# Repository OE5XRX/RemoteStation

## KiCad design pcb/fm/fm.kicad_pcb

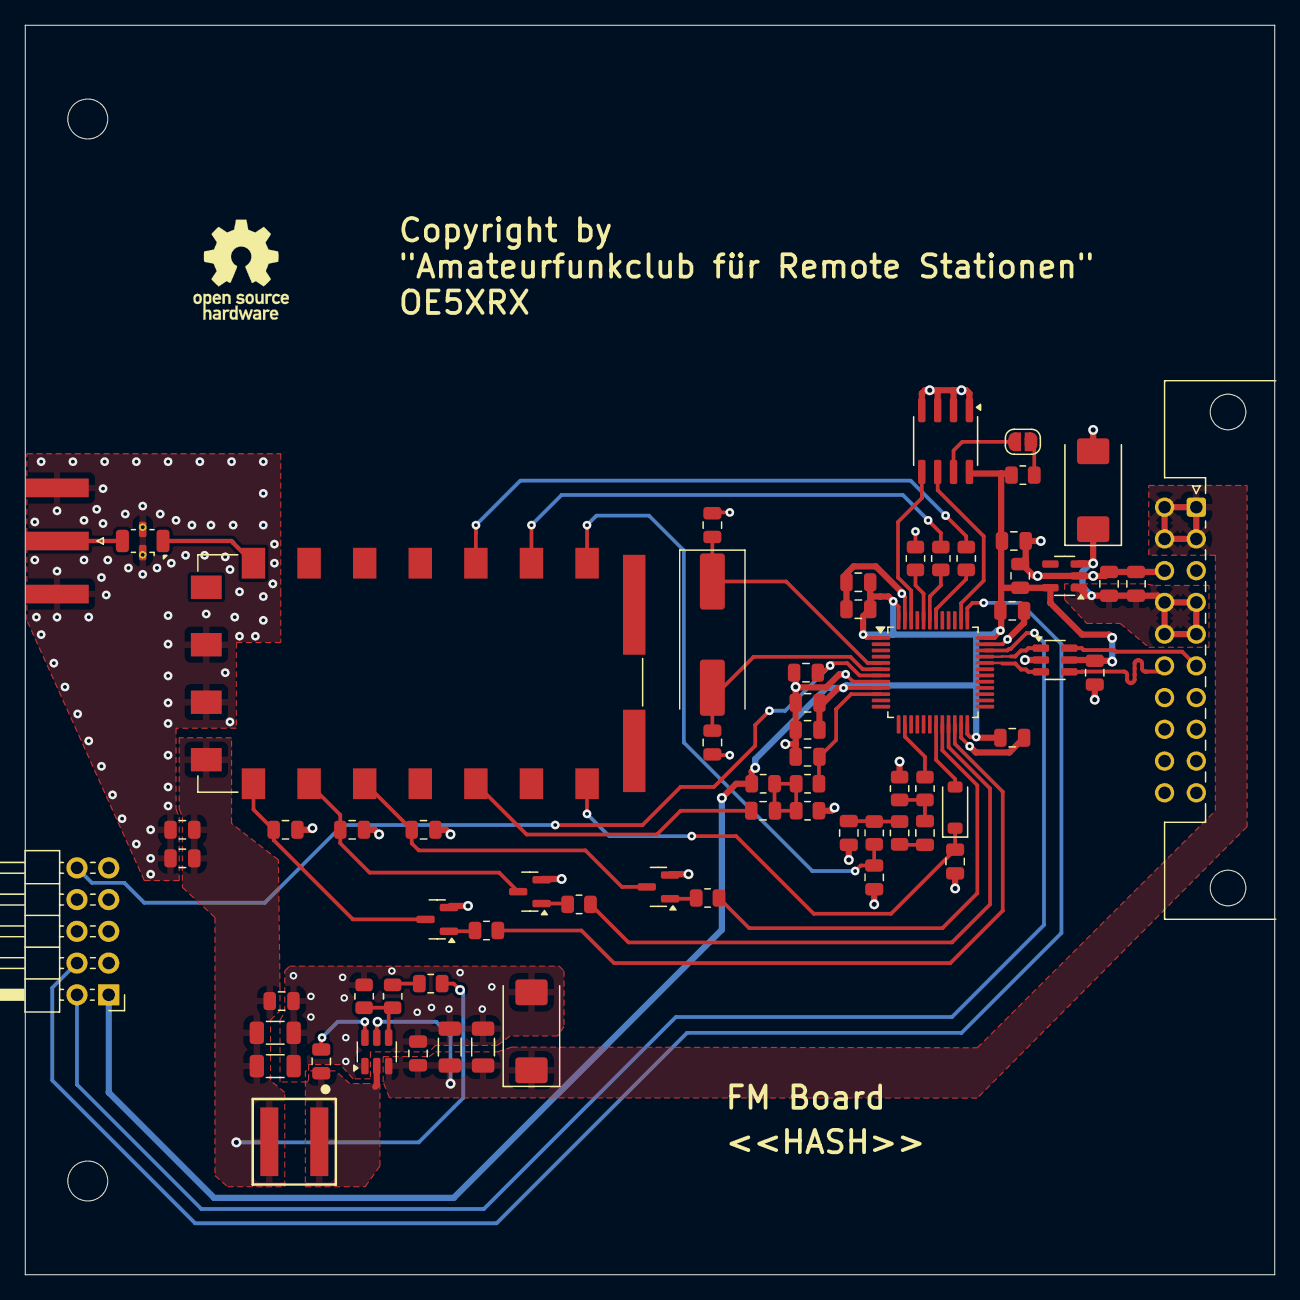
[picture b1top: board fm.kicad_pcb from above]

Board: 4 copper layers, 100.0 x 100.0 mm, 70 parts (0 on the bottom side), 48 nets.

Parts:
C101, C201, C202, C204, C206, C208, C210, C214, C215: 100nF; C_0805_2012Metric
C102: 10uF; C_0805_2012Metric
C103, C402, C501, C601, C701: 10nF/NP0; C_0805_2012Metric
C104, C213: 100u / 25V; CP_EIA-7343-43_Kemet-X
C203, C205: 30pF; C_0805_2012Metric
C207, C209, C301, C401: 4.7u/10V/X5R; C_0805_2012Metric
C211, C212: 1uF; C_0805_2012Metric
C302, C303: 5.6nF/X7R/100V; C_0805_2012Metric
C802, C803: 10u; C_1206_3216Metric
C804, C805, C808: 100n; C_0805_2012Metric
C806, C807: 22u; C_1206_3216Metric
D101: BAT43W-V; D_SOD-123
FL101: LFCN-180/490; Filter_Mini-Circuits_FV1206
H101, H102: MountingHole; MountingHole_3.2mm_M3
J101: Conn_Coaxial; SMA_Amphenol_132289_EdgeMount
J201: Conn_ARM_JTAG_SWD_10; PinHeader_2x05_P2.54mm_Horizontal
J202: Conn_02x10_Row_Letter_First; PCN10C-20S-2.54DS
JP201: SolderJumper_2_Open; SolderJumper-2_P1.3mm_Open_RoundedPad1.0x1.5mm
L801: 6.8u; WE-XHMI_6060
Q501, Q601, Q701: 2N7002; SOT-23
R101, R102: 220; R_0805_2012Metric
R201, R403: 2k2; R_0805_2012Metric
R202: 3k9; R_0805_2012Metric
R301: 56k; R_0805_2012Metric
R302, R303, R304, R501, R601, R701: 10k; R_0805_2012Metric
R401, R402: 5k1; R_0805_2012Metric
R801: 49R9; R_0805_2012Metric
R802: 100k; R_0805_2012Metric
R803: 13k7; R_0805_2012Metric
U101: SA818V; DRA818
U201: STM32F302CBTx; LQFP-48_7x7mm_P0.5mm
U202: CAT24C32; SOIC-8_3.9x4.9mm_P1.27mm
U203: TLV73333PQDBVRQ1; SOT-23-5
U204: USBLC6-2SC6; SOT-23-6
U801: LMR51430 500kHz; SOT-23-6
Y201: 8MHz / 20pF; Crystal_SMD_HC49-SD

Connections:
+3V3: C202.2, C204.2, C206.2, C207.2, C208.2, C209.2, C212.1, C214.2, C215.1, J201.1 (VTref), R202.1, R401.2, U201.1 (VBAT), U201.9 (VDDA), U201.24 (VDD), U201.36 (VDD), U201.48 (VDD), U202.8 (VCC), U203.5 (OUT), U204.5 (VBUS)
+5V: C210.2, C211.1, C213.1, J202.a4, J202.a5, J202.b4, J202.b5, U203.1 (IN), U203.3 (EN)
+5V_HF: C101.2, C102.2, C806.2, C807.2, C808.2, L801.2, R801.1, U101.8 (VDD)
+12V: C104.1, C802.1, C803.1, C804.1, J202.a1, J202.a2, J202.b1, J202.b2, U801.3 (VIN), U801.5 (EN)
/5V/TPS_SW: C805.2, L801.1, U801.2 (SW)
/ADC: C402.2, R403.2, U201.10 (PA0)
/AF_OUT: C401.2, U101.3 (AF_OUT)
/ANT: FL101.3 (OUT), J101.1 (In)
/Connector and CPU/GPIO4: D101.2 (A), U201.19 (PB1)
/Connector and CPU/I2C_SCL_MEM: U201.38 (PA15), U202.6 (SCL)
/Connector and CPU/I2C_SDA_MEM: U201.46 (PB9), U202.5 (SDA)
/Connector and CPU/NS_USB+: U201.33 (PA12), U204.1 (I/O1)
/Connector and CPU/NS_USB-: U201.32 (PA11), U204.3 (I/O2)
/Connector and CPU/SWCLK: J201.4 (SWCLK/TCK), U201.37 (PA14)
/Connector and CPU/SWDIO: J201.2 (SWDIO/TMS), U201.34 (PA13)
/Connector and CPU/USART_RX: R102.2, U201.43 (PB7)
/Connector and CPU/USART_TX: R101.2, U201.42 (PB6)
/Connector and CPU/USB+: J202.a6, U204.6 (I/O1)
/Connector and CPU/USB-: J202.b6, U204.4 (I/O2)
/Connector and CPU/nRESET: C201.1, J201.10 (~RESET), U201.7 (NRST)
/DAC: R301.1, U201.14 (PA4)
/GPIO1: R601.1, U201.20 (PB2)
/GPIO2: R701.1, U201.21 (PB10)
/GPIO3: R501.1, U201.22 (PB11)
/H_L_Power: C501.2, Q501.3 (D), U101.7 (H/L)
/LPF: FL101.1 (IN), U101.12 (ANT)
/MIC_IN: C303.1, R304.2, U101.18 (MIC_IN)
/RADIO_RX: R101.1, U101.16 (RXD)
/RADIO_TX: R102.1, U101.17 (TXD)
/nPOWER_DOWN: C701.2, Q701.3 (D), U101.6 (~PD)
/nPTT: C601.2, Q601.3 (D), U101.5 (~PTT)
/nSQUELCH: C103.2, D101.1 (K), U101.1 (~SQ)
GND: C101.1, C102.1, C103.1, C104.2, C201.2, C202.1, C203.2, C204.1, C205.2, C206.1, C207.1, C208.1, C209.1, C210.1, C211.2, C212.2, C213.2, C214.1, C215.2, C302.2, C303.2, C402.1, C501.1, C601.1, C701.1, C802.2, C803.2, C804.2, C806.1, C807.1, C808.1, FL101.2 (GND), FL101.4 (GND), J101.2 (Ext), J201.3 (GND), J201.5 (GND), J201.9 (GNDDetect), J202.a3, J202.a10, J202.b3, J202.b10, Q501.2 (S), Q601.2 (S), Q701.2 (S), R201.2, R302.2, R402.1, R803.2, U101.9 (GND), U101.10 (GND), U201.8 (VSSA), U201.23 (VSS), U201.35 (VSS), U201.47 (VSS), U202.1 (A0), U202.2 (A1), U202.3 (A2), U202.4 (GND), U203.2 (GND), U204.2 (GND), U801.1 (GND)
unnamed: C301.1, R303.1
unnamed: C301.2, R301.2, R302.1
unnamed: C302.1, R303.2, R304.1
unnamed: C401.1, R401.1, R402.2, R403.1
unnamed: JP201.1 (A), U202.7 (WP)
unnamed: JP201.2 (B), R202.2
unnamed: Q501.1 (G), R501.2
unnamed: Q601.1 (G), R601.2
unnamed: Q701.1 (G), R701.2
unnamed: R801.2, R802.1
unnamed: R201.1, U201.44 (BOOT0)
unnamed: C203.1, U201.5 (PF0), Y201.1
unnamed: C205.1, U201.6 (PF1), Y201.2
unnamed: C805.1, U801.6 (CB)
unnamed: R802.2, R803.1, U801.4 (FB)

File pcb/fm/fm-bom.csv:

Row,Description,Part,References,Value,Footprint,Quantity Per PCB,Status,Datasheet,LCSC,MOUSER,SnapEDA_Link
1,Unpolarized capacitor,C,C203 C205,30pF,C_0805_2012Metric,2, ,~,,791-0805N300J500CT,
2,Unpolarized capacitor,C,C302 C303,5.9nF,C_0805_2012Metric,2, ,~,,,
3,Unpolarized capacitor,C,C103 C402 C501 C601 C701,10nF/NP0,C_0805_2012Metric,5, ,~,,81-GRM2165C2A103JA1D,
4,Unpolarized capacitor,C,C101 C106 C201 C202 C204 C206 C208 C210 C214,100nF,C_0805_2012Metric,9, ,~,C28233,,
5,Unpolarized capacitor,C,C104 C211 C212,1uF,C_0805_2012Metric,3, ,~,,791-0805B105K250CT,
6,Unpolarized capacitor,C,C105,2.2uF,C_0805_2012Metric,1, ,~,,187-CL21B225KOFNNNG,
7,Unpolarized capacitor,C,C102,10uF,C_0805_2012Metric,1, ,~,,963-EMK212BJ106KG-T,
8,Polarized capacitor,C_Polarized,C213,100u / 25V,CP_EIA-7343-43_Kemet-X,1, ,~,C132558,,
9,Unpolarized capacitor,C,C207 C209 C301 C401,4.7u/10V/X5R,C_0805_2012Metric,4, ,~,,187-CL21A475KAQNNNF,
10,"30V 0.2A Small Signal Schottky diode, SOD-123",BAT43W-V,D101,BAT43W-V,D_SOD-123,1, ,http://www.vishay.com/docs/85660/bat42.pdf,,78-BAT43W-G3-08,
11,"180MHz/490MHz 50 Ohm Passive Low Pass Filter, FV1206",LFCN-160,FL101,LFCN-180/490,Filter_Mini-Circuits_FV1206,1, ,https://www.minicircuits.com/pdfs/LFCN-180+.pdf,,139-LFCN-180 / 139-LFCN-490,
12,"Generic connector, double row, 02x10, row letter first pin numbering scheme (pin number consists of a letter for the row and a number for the pin index in this row. a1, ..., aN; b1, ..., bN), script generated (kicad-library-utils/schlib/autogen/connector/)",Conn_02x10_Row_Letter_First,J202,Conn_02x10_Row_Letter_First,PCN10C-20S-2.54DS,1, ,~,,798-PCN10C20S254DS72,
13,"Cortex Debug Connector, standard ARM Cortex-M SWD and JTAG interface",Conn_ARM_JTAG_SWD_10,J201,Conn_ARM_JTAG_SWD_10,PinHeader_2x05_P2.54mm_Horizontal,1, ,http://infocenter.arm.com/help/topic/com.arm.doc.ddi0314h/DD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,,,
14,"coaxial connector (BNC, SMA, SMB, SMC, Cinch/RCA, LEMO, ...)",Conn_Coaxial,J101,Conn_Coaxial,SMA_Amphenol_132289_EdgeMount,1, ,~,,530-142-0701-801,
15,"0.115A Id, 60V Vds, N-Channel MOSFET, SOT-23",2N7002,Q501 Q601 Q701,2N7002,SOT-23,3, ,https://www.onsemi.com/pub/Collateral/NDS7002A-D.PDF,,637-2N7002,
16,Resistor,R,R101 R102,220,R_0805_2012Metric,2, ,~,,667-ERA-6AEB221V,
17,Resistor,R,R201 R403,2k2,R_0805_2012Metric,2, ,~,C17520,,
18,Resistor,R,R202,3k9,R_0805_2012Metric,1, ,~,,603-RT0805DRD073K9L,
19,Resistor,R,R401 R402,5k1,R_0805_2012Metric,2, ,~,C27834,,
20,Resistor,R,R302 R303 R304 R501 R601 R701,10k,R_0805_2012Metric,6, ,~,,603-RT0805DRE0710KL,
21,Resistor,R,R301,56k,R_0805_2012Metric,1, ,~,,,
22,"32 kb CMOS Serial EEPROM, SOIC-8/TSSOP-8/DFN-8",CAT24C128,U202,CAT24C32,SOIC-8_3.9x4.9mm_P1.27mm,1, ,,,698-CAT24C32WI-GT3,
23,,SA818V,U101,SA818V,DRA818,1, ,,C3001504,,https://www.snapeda.com/parts/DRA818V/DORJI/view-part/?ref=snap
24,"STMicroelectronics Arm Cortex-M4 MCU, 128KB flash, 32KB RAM, 72 MHz, 2.0-3.6V, 37 GPIO, LQFP48",STM32F302CBTx,U201,STM32F302CBTx,LQFP-48_7x7mm_P0.5mm,1, ,https://www.st.com/resource/en/datasheet/stm32f302cb.pdf,,511-STM32F302CBT7,
25,"300mA Capacitor-Free Low Dropout Voltage Regulator, Fixed Output 3.3V, SOT-23-5",TLV73333PDBV,U203,TLV73333PQDBVRQ1,SOT-23-5,1, ,http://www.ti.com/lit/ds/symlink/tlv733p.pdf,C2862550,595-TLV73333PQDBVRQ1,
26,,XC6220B331MR,U102,XC6227C401PR-G,SOT-89-5,1, ,,,865-XC6227C401PR-G,
27,Two pin crystal,Crystal,Y201,8MHz / 20pF,Crystal_SMD_HC49-SD,1, ,~,,73-XT49M800-20,

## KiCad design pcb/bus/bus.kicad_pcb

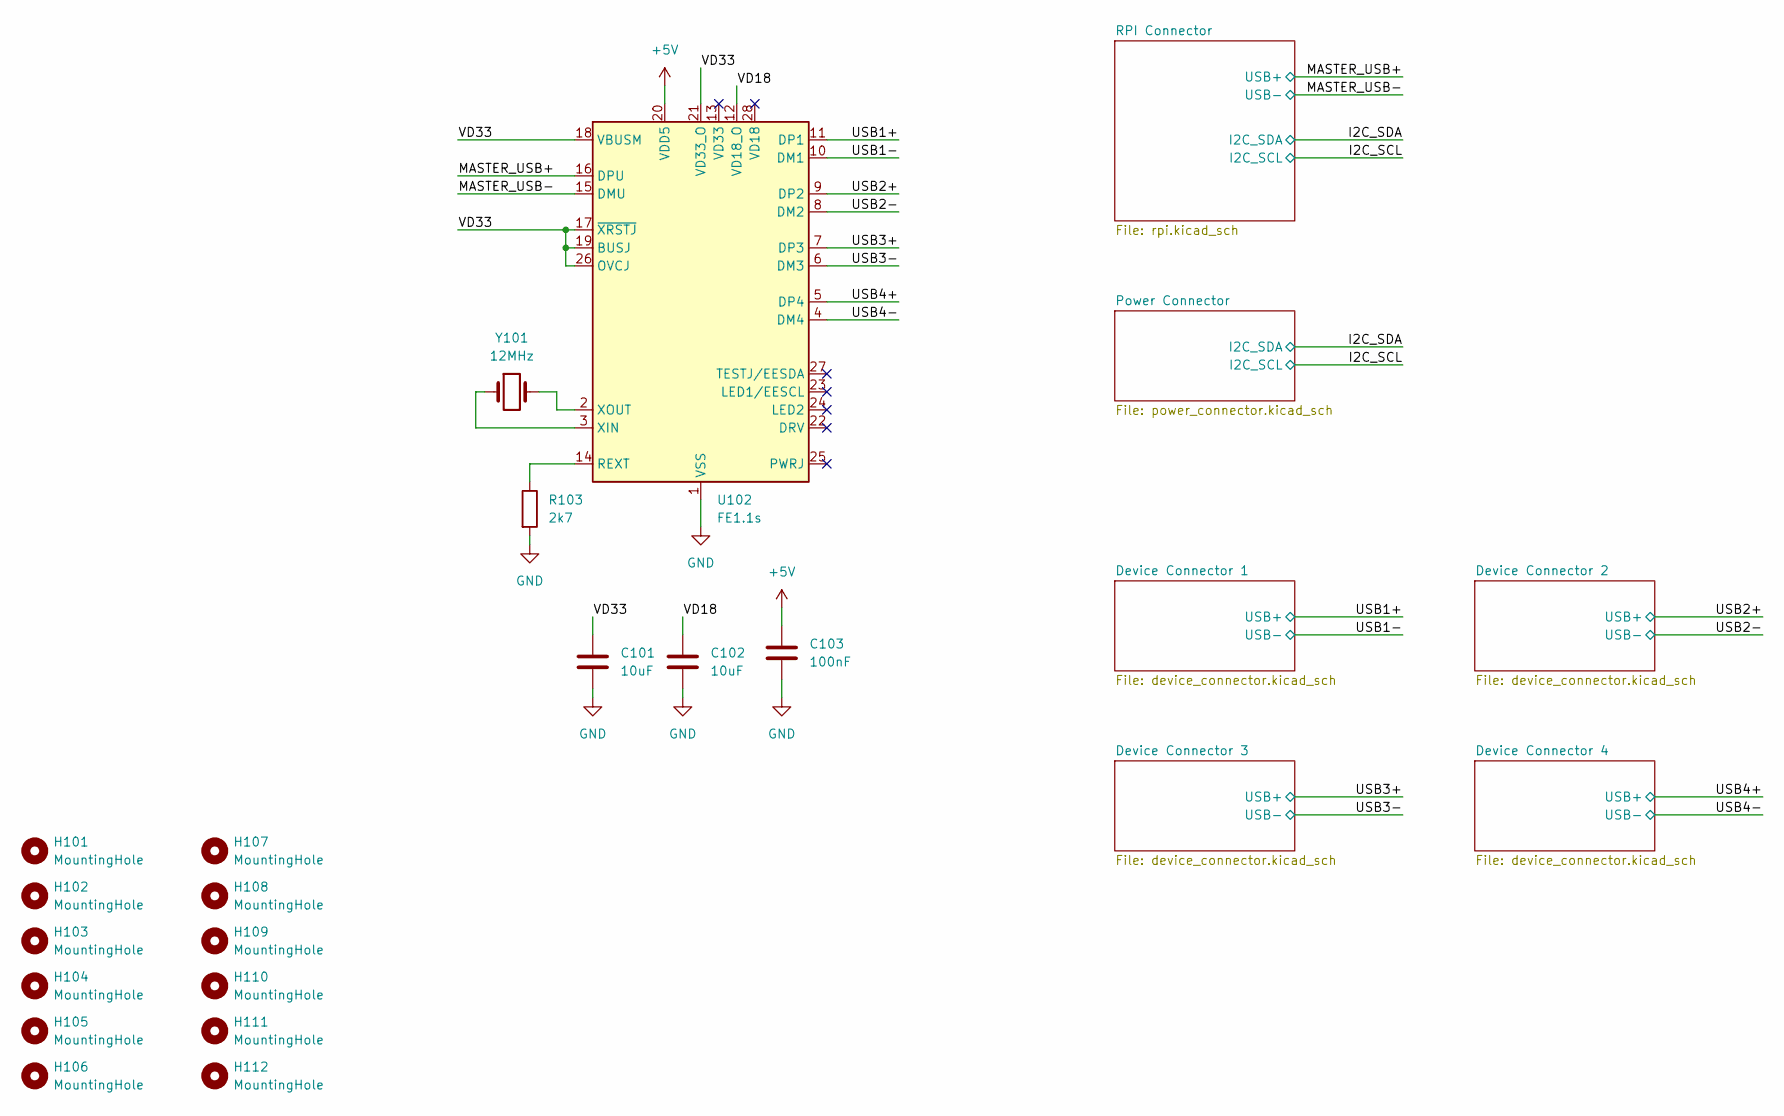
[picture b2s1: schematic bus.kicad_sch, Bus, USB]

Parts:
C101, C102: 10uF; C_0805_2012Metric; LCSC C13585
C103: 100nF; C_0805_2012Metric; LCSC C28233
H101, H102, H103, H104, H105, H106, H107, H108, H109, H110, H111, H112: MountingHole; MountingHole_3.2mm_M3
R103: 2k7; R_0805_2012Metric; LCSC C352230
U102: FE1.1s; SSOP-28_3.9x9.9mm_P0.635mm; LCSC C6706491
Y101: 12MHz; M49S-SMD; LCSC C2983432

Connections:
+5V: C103.1, U102.20 (VDD5); also elsewhere on the board
/MASTER_USB+: U102.16 (DPU); also elsewhere on the board
/MASTER_USB-: U102.15 (DMU); also elsewhere on the board
/USB1+: U102.5 (DP4); also elsewhere on the board
/USB1-: U102.4 (DM4); also elsewhere on the board
/USB2+: U102.7 (DP3); also elsewhere on the board
/USB2-: U102.6 (DM3); also elsewhere on the board
/USB3+: U102.9 (DP2); also elsewhere on the board
/USB3-: U102.8 (DM2); also elsewhere on the board
/USB4+: U102.11 (DP1); also elsewhere on the board
/USB4-: U102.10 (DM1); also elsewhere on the board
/VD18: C102.1, U102.12 (VD18_O)
/VD33: C101.1, U102.17 (~XRSTJ), U102.18 (VBUSM), U102.19 (BUSJ), U102.21 (VD33_O), U102.26 (OVCJ)
GND: C101.2, C102.2, C103.2, R103.2, U102.1 (VSS); also elsewhere on the board
unnamed: R103.1, U102.14 (REXT)
unnamed: U102.3 (XIN), Y101.1
unnamed: U102.2 (XOUT), Y101.2

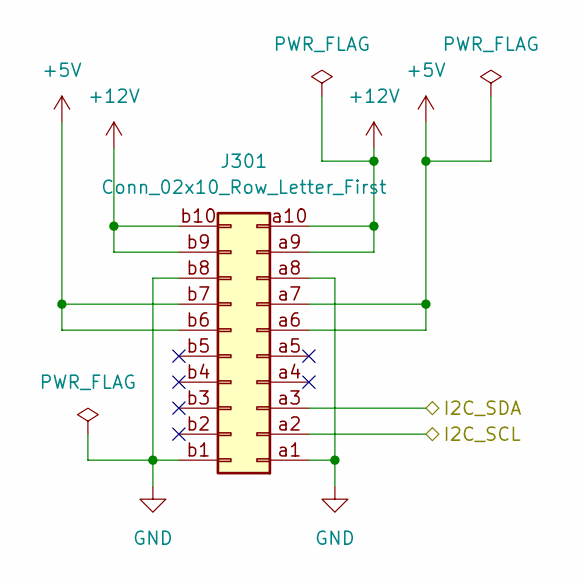
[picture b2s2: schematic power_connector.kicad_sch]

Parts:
J301: Conn_02x10_Row_Letter_First; PCN10-20P-2.54DSA

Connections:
+5V: J301.a6, J301.a7, J301.b6, J301.b7; also elsewhere on the board
+12V: J301.a9, J301.a10, J301.b9, J301.b10; also elsewhere on the board
/I2C_SCL: J301.a2; also elsewhere on the board
/I2C_SDA: J301.a3; also elsewhere on the board
GND: J301.a1, J301.a8, J301.b1, J301.b8; also elsewhere on the board

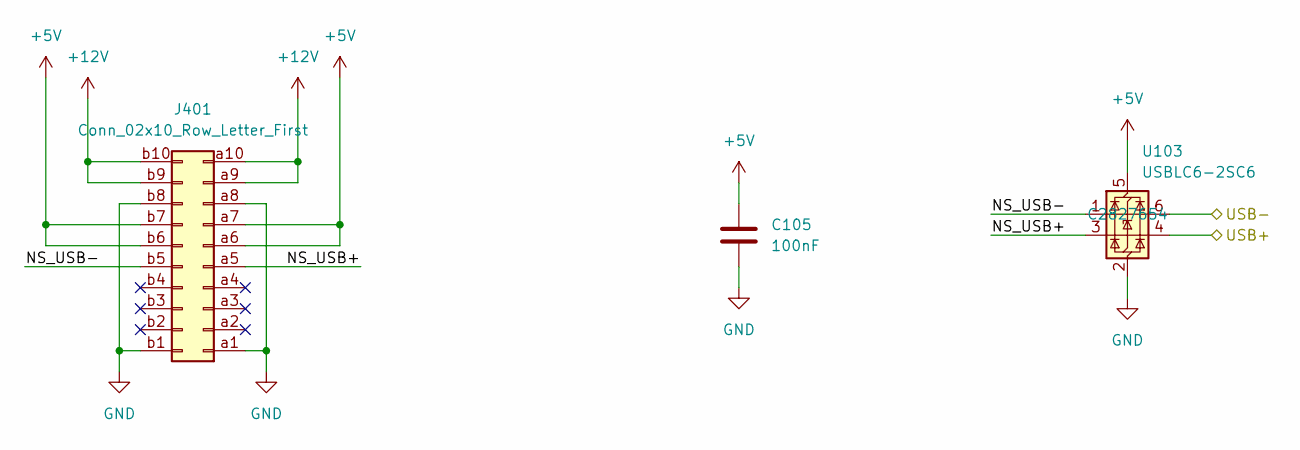
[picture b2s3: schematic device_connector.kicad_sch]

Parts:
C105: 100nF; C_0805_2012Metric; LCSC C28233
J401: Conn_02x10_Row_Letter_First; PCN10-20P-2.54DSA; MOUSER 798-PCN1020P254DSA72
U103: USBLC6-2SC6; SOT-666; LCSC C2827654

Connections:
+5V: C105.1, J401.a6, J401.a7, J401.b6, J401.b7, U103.5 (VBUS); also elsewhere on the board
+12V: J401.a9, J401.a10, J401.b9, J401.b10; also elsewhere on the board
/Device Connector 1/NS_USB+: J401.a5, U103.3 (I/O2)
/Device Connector 1/NS_USB-: J401.b5, U103.1 (I/O1)
/USB1+: U103.4 (I/O2); also elsewhere on the board
/USB1-: U103.6 (I/O1); also elsewhere on the board
GND: C105.2, J401.a1, J401.a8, J401.b1, J401.b8, U103.2 (GND); also elsewhere on the board

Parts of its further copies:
C106, C107, C108: 100nF; C_0805_2012Metric; LCSC C28233
J501, J601, J701: Conn_02x10_Row_Letter_First; PCN10-20P-2.54DSA; MOUSER 798-PCN1020P254DSA72
U104, U105, U106: USBLC6-2SC6; SOT-666; LCSC C2827654

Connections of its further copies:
+5V: C106.1, C107.1, C108.1, J501.a6, J501.a7, J501.b6, J501.b7, J601.a6, J601.a7, J601.b6, J601.b7, J701.a6, J701.a7, J701.b6, J701.b7, U104.5 (VBUS), U105.5 (VBUS), U106.5 (VBUS); also elsewhere on the board
+12V: J501.a9, J501.a10, J501.b9, J501.b10, J601.a9, J601.a10, J601.b9, J601.b10, J701.a9, J701.a10, J701.b9, J701.b10; also elsewhere on the board
/Device Connector 2/NS_USB+: J501.a5, U104.3 (I/O2)
/Device Connector 2/NS_USB-: J501.b5, U104.1 (I/O1)
/Device Connector 3/NS_USB+: J601.a5, U105.3 (I/O2)
/Device Connector 3/NS_USB-: J601.b5, U105.1 (I/O1)
/Device Connector 4/NS_USB+: J701.a5, U106.3 (I/O2)
/Device Connector 4/NS_USB-: J701.b5, U106.1 (I/O1)
/USB2+: U104.4 (I/O2); also elsewhere on the board
/USB2-: U104.6 (I/O1); also elsewhere on the board
/USB3+: U105.4 (I/O2); also elsewhere on the board
/USB3-: U105.6 (I/O1); also elsewhere on the board
/USB4+: U106.4 (I/O2); also elsewhere on the board
/USB4-: U106.6 (I/O1); also elsewhere on the board
GND: C106.2, C107.2, C108.2, J501.a1, J501.a8, J501.b1, J501.b8, J601.a1, J601.a8, J601.b1, J601.b8, J701.a1, J701.a8, J701.b1, J701.b8, U104.2 (GND), U105.2 (GND), U106.2 (GND); also elsewhere on the board

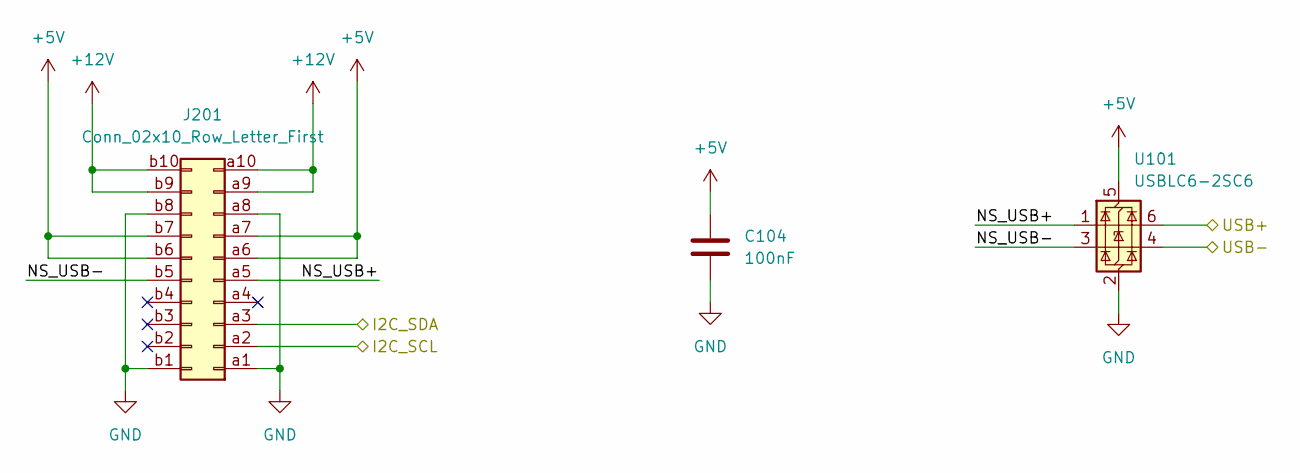
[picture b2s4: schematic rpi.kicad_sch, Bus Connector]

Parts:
C104: 100nF; C_0805_2012Metric; LCSC C28233
J201: Conn_02x10_Row_Letter_First; PCN10-20P-2.54DSA; MOUSER 798-PCN1020P254DSA72
U101: USBLC6-2SC6; SOT-666; LCSC C2827654

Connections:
+5V: C104.1, J201.a6, J201.a7, J201.b6, J201.b7, U101.5 (VBUS); also elsewhere on the board
+12V: J201.a9, J201.a10, J201.b9, J201.b10; also elsewhere on the board
/I2C_SCL: J201.a2; also elsewhere on the board
/I2C_SDA: J201.a3; also elsewhere on the board
/MASTER_USB+: U101.6 (I/O1); also elsewhere on the board
/MASTER_USB-: U101.4 (I/O2); also elsewhere on the board
/RPI Connector/NS_USB+: J201.a5, U101.1 (I/O1)
/RPI Connector/NS_USB-: J201.b5, U101.3 (I/O2)
GND: C104.2, J201.a1, J201.a8, J201.b1, J201.b8, U101.2 (GND); also elsewhere on the board

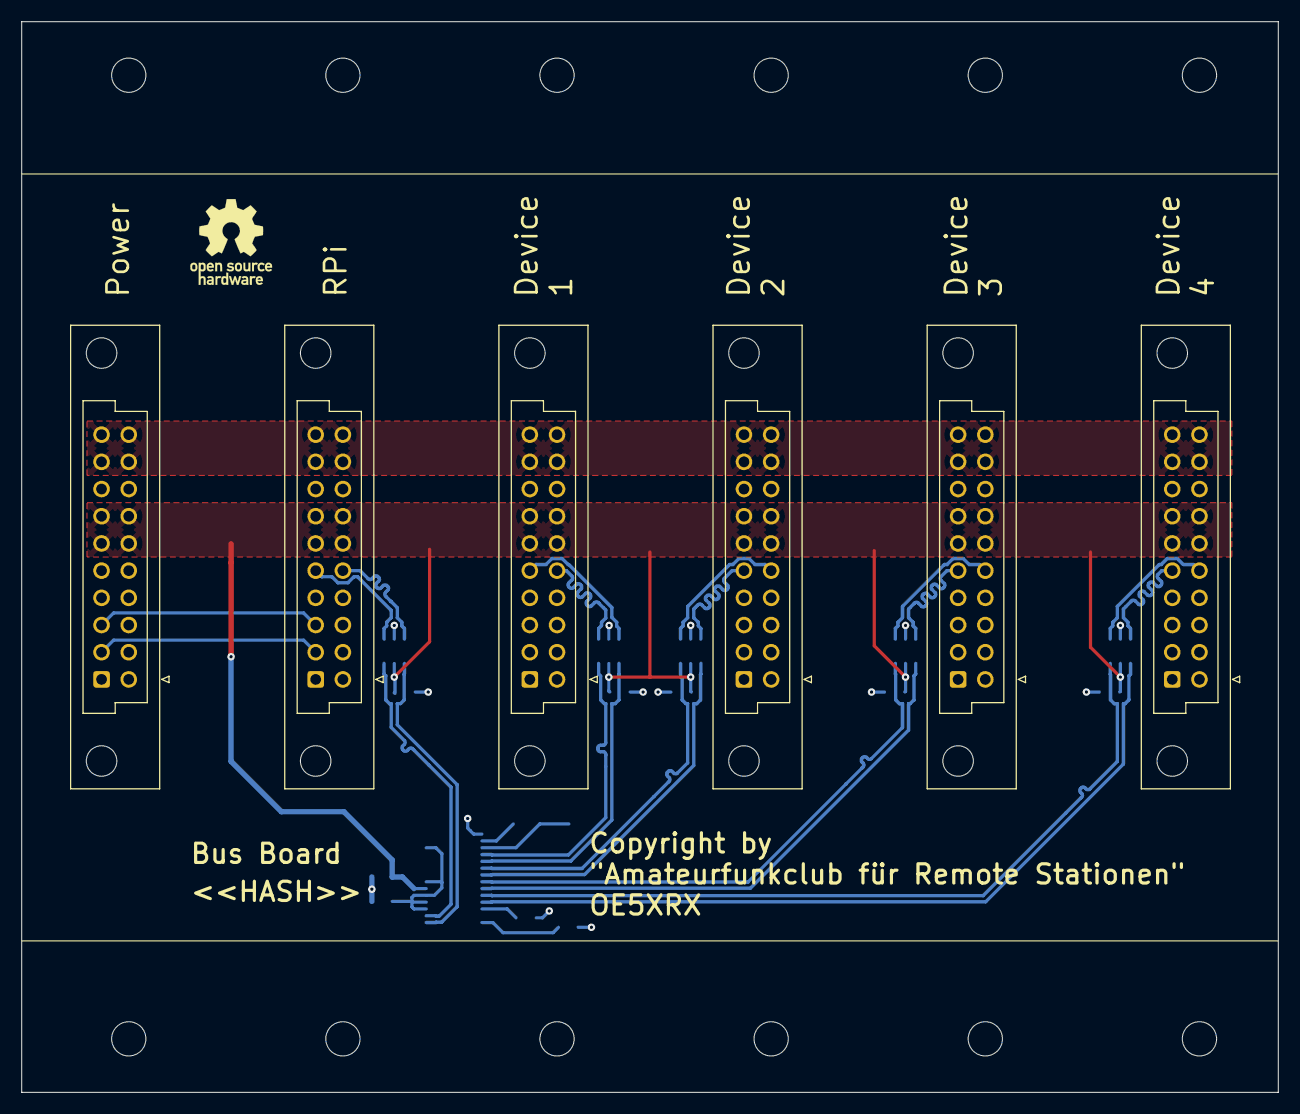
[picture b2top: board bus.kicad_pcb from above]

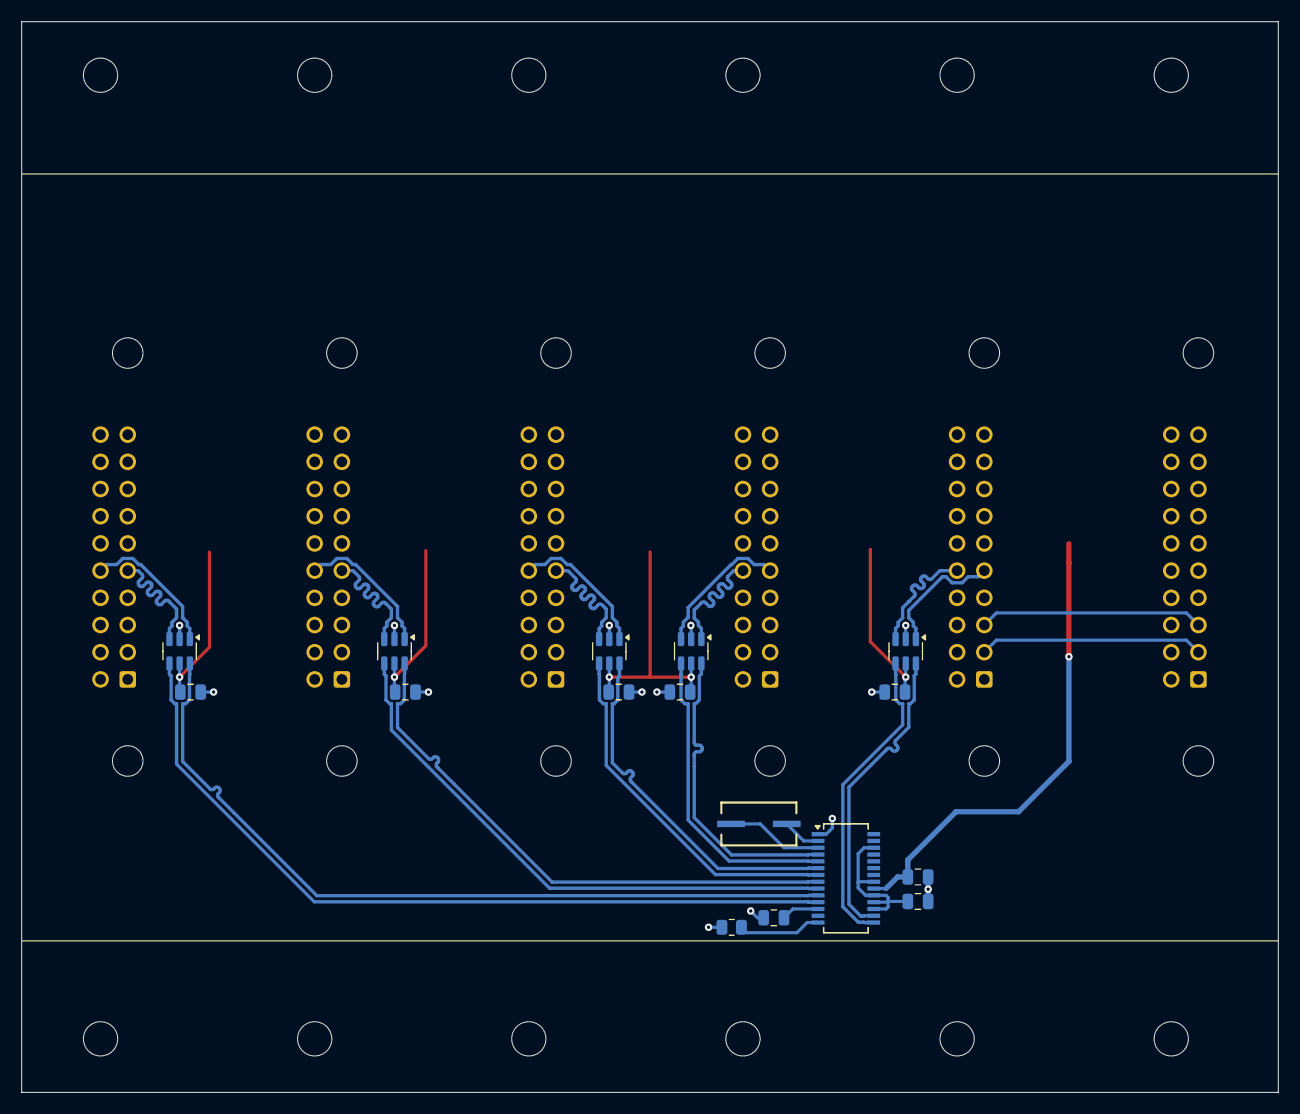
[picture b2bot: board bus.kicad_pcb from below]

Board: 4 copper layers, 117.4 x 100.0 mm, 34 parts (16 on the bottom side), 30 nets.

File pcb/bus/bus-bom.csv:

Row,Description,Part,References,Value,Footprint,Quantity Per PCB,Status,Datasheet,LCSC,MOUSER
1,Unpolarized capacitor,C,C103 C104 C105 C106 C107 C108,100nF,C_0805_2012Metric,6, ,~,C28233,
2,Unpolarized capacitor,C,C101 C102,10uF,C_0805_2012Metric,2, ,~,C13585,
3,"Generic connector, double row, 02x10, row letter first pin numbering scheme (pin number consists of a letter for the row and a number for the pin index in this row. a1, ..., aN; b1, ..., bN), script generated (kicad-library-utils/schlib/autogen/connector/)",Conn_02x10_Row_Letter_First,J201 J301 J401 J501 J601 J701,Conn_02x10_Row_Letter_First,PCN10-20P-2.54DSA,6, ,~,,798-PCN1020P254DSA72
4,Resistor,R,R103,2k7,R_0805_2012Metric,1, ,~,C352230,
5,"USB 2.0 High Speed 4-Port Hub Controller, SSOP-28",FE1.1s,U102,FE1.1s,SSOP-28_3.9x9.9mm_P0.635mm,1, ,https://cdn-shop.adafruit.com/product-files/2991/FE1.1s+Data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,C6706491,
6,"Very low capacitance ESD protection diode, 2 data-line, SOT-23-6",USBLC6-2SC6,U101 U103 U104 U105 U106,USBLC6-2SC6,SOT-666,5, ,https://www.st.com/resource/en/datasheet/usblc6-2.pdf,C2827654,
7,Two pin crystal,Crystal,Y101,12MHz,M49S-SMD,1, ,~,C2983432,

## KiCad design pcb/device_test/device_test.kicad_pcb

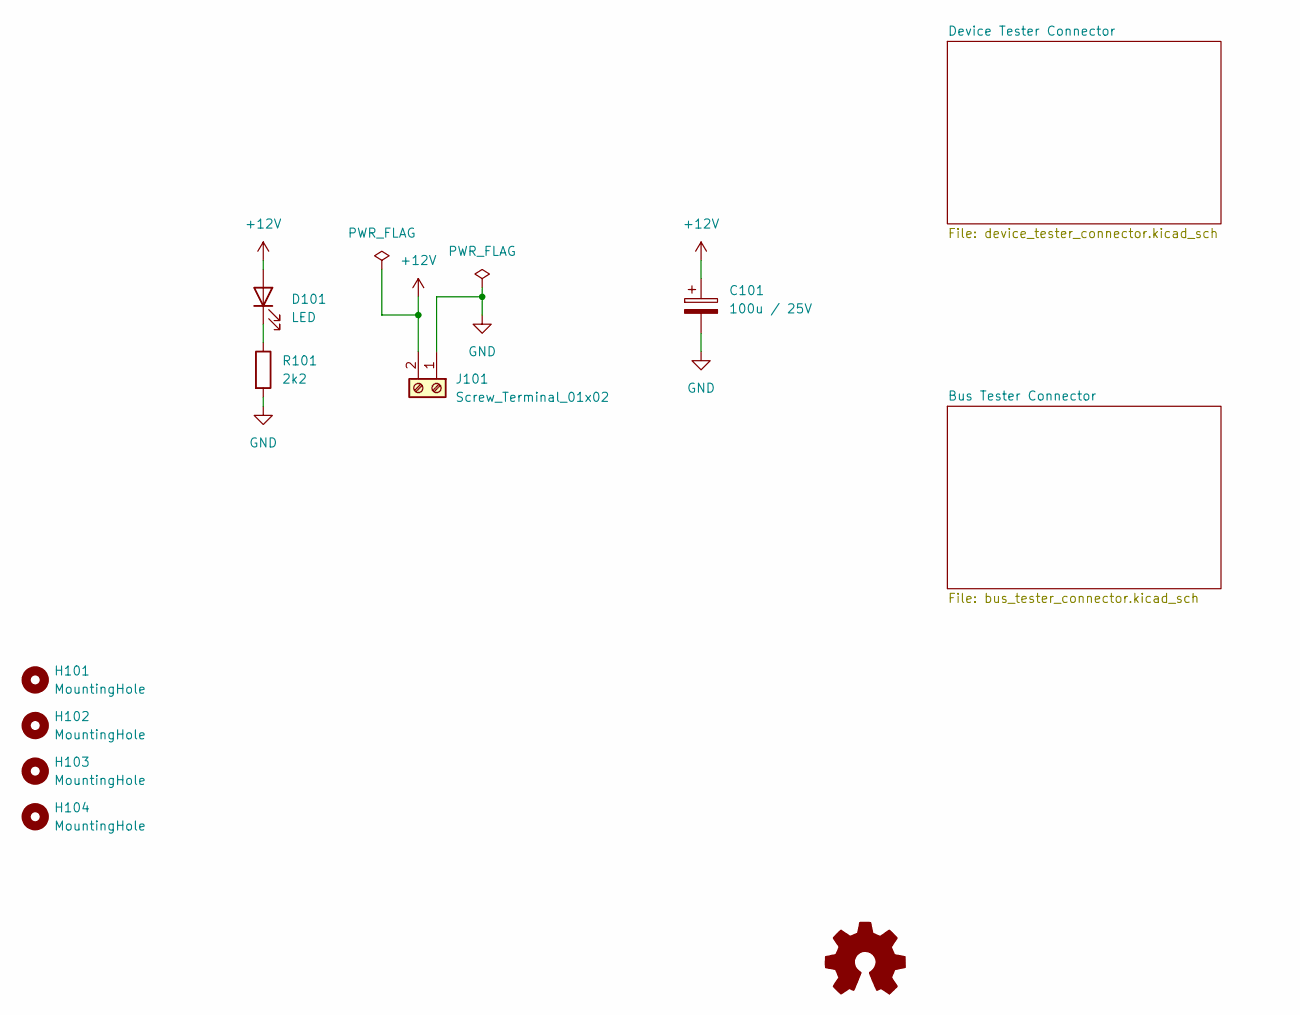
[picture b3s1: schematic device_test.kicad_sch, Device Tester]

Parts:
C101: 100u / 25V; CP_EIA-7343-43_Kemet-X; LCSC C132558
D101: LED; LED_0805_2012Metric; LCSC C84256
H101, H102, H103, H104: MountingHole; MountingHole_3.2mm_M3
J101: Screw_Terminal_01x02; TerminalBlock_Phoenix_MKDS-1,5-2-5.08_1x02_P5.08mm_Horizont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; LCSC C5349557
R101: 2k2; R_0805_2012Metric; LCSC C17520

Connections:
+12V: C101.1, D101.2 (A), J101.2; also elsewhere on the board
GND: C101.2, J101.1, R101.2; also elsewhere on the board
unnamed: D101.1 (K), R101.1

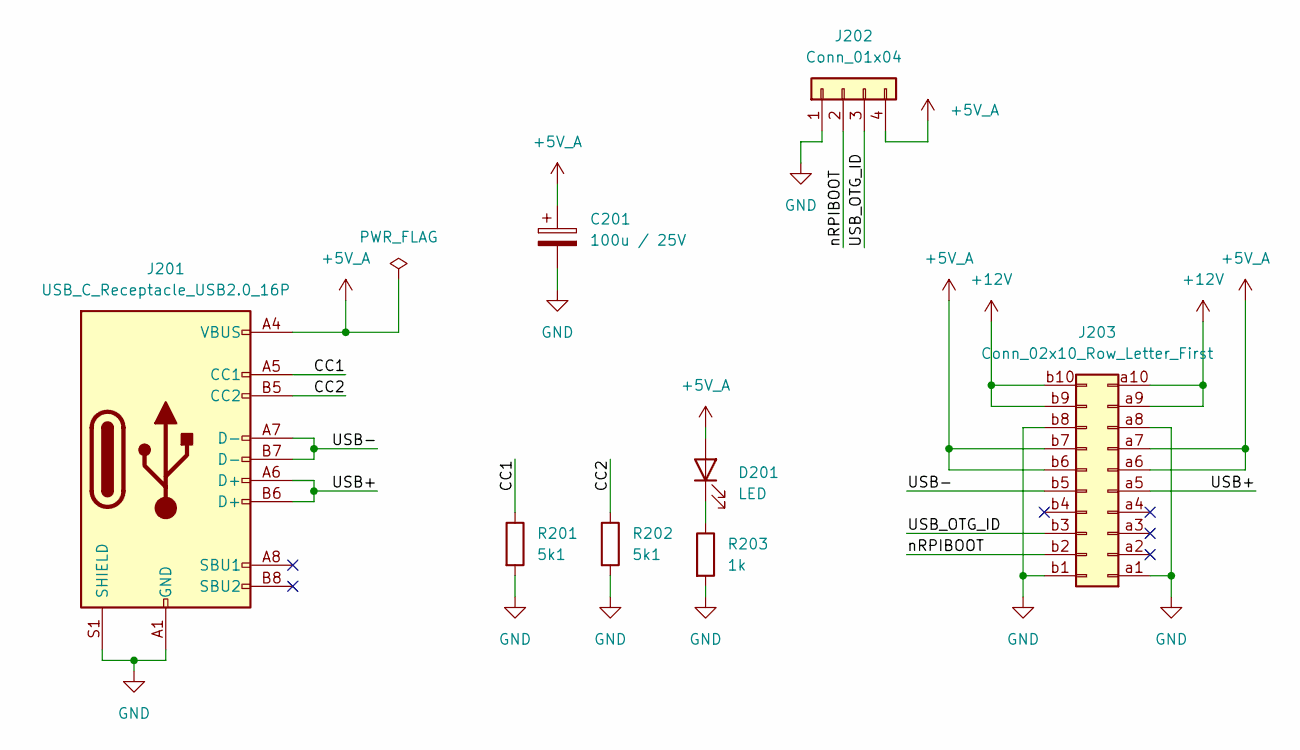
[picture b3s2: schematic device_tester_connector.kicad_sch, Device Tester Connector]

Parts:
C201: 100u / 25V; CP_EIA-7343-43_Kemet-X; LCSC C132558
D201: LED; LED_0805_2012Metric; LCSC C84256
J201: USB_C_Receptacle_USB2.0_16P; USB_C_Receptacle_G-Switch_GT-USB-7010ASV; LCSC C2988369
J202: Conn_01x04; PinHeader_1x04_P2.54mm_Vertical; LCSC C2691448
J203: Conn_02x10_Row_Letter_First; PCN10-20P-2.54DS; MOUSER 798-PCN1020P254DS72
R201, R202: 5k1; R_0805_2012Metric; LCSC C27834
R203: 1k; R_0805_2012Metric; LCSC C17513

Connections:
+5V_A: C201.1, D201.2 (A), J201.A4 (VBUS), J201.A9 (VBUS), J201.B4 (VBUS), J201.B9 (VBUS), J202.4, J203.a6, J203.a7, J203.b6, J203.b7
+12V: J203.a9, J203.a10, J203.b9, J203.b10; also elsewhere on the board
/Device Tester Connector/CC1: J201.A5 (CC1), R201.1
/Device Tester Connector/CC2: J201.B5 (CC2), R202.1
/Device Tester Connector/USB+: J201.A6 (D+), J201.B6 (D+), J203.a5
/Device Tester Connector/USB-: J201.A7 (D-), J201.B7 (D-), J203.b5
/Device Tester Connector/USB_OTG_ID: J202.3, J203.b3
/Device Tester Connector/nRPIBOOT: J202.2, J203.b2
GND: C201.2, J201.A1 (GND), J201.A12 (GND), J201.B1 (GND), J201.B12 (GND), J201.S1 (SHIELD), J202.1, J203.a1, J203.a8, J203.b1, J203.b8, R201.2, R202.2, R203.2; also elsewhere on the board
unnamed: D201.1 (K), R203.1

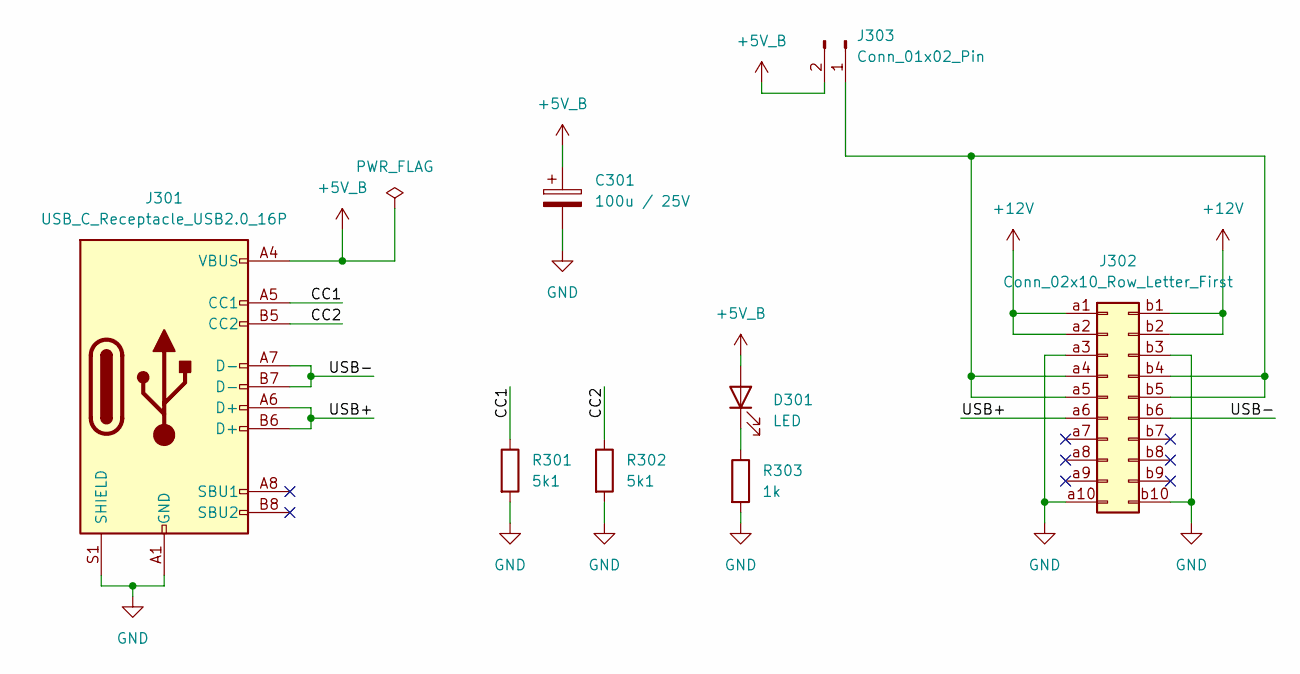
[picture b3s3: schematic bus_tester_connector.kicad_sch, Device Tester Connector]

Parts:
C301: 100u / 25V; CP_EIA-7343-43_Kemet-X; LCSC C132558
D301: LED; LED_0805_2012Metric; LCSC C84256
J301: USB_C_Receptacle_USB2.0_16P; USB_C_Receptacle_G-Switch_GT-USB-7010ASV; LCSC C2988369
J302: Conn_02x10_Row_Letter_First; PCN10C-20S-2.54DS; MOUSER 798-PCN10C20S254DS72
J303: Conn_01x02_Pin; PinHeader_1x02_P2.54mm_Vertical
R301, R302: 5k1; R_0805_2012Metric; LCSC C27834
R303: 1k; R_0805_2012Metric; LCSC C17513

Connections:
+5V_B: C301.1, D301.2 (A), J301.A4 (VBUS), J301.A9 (VBUS), J301.B4 (VBUS), J301.B9 (VBUS), J303.2
+12V: J302.a1, J302.a2, J302.b1, J302.b2; also elsewhere on the board
/Bus Tester Connector/CC1: J301.A5 (CC1), R301.1
/Bus Tester Connector/CC2: J301.B5 (CC2), R302.1
/Bus Tester Connector/USB+: J301.A6 (D+), J301.B6 (D+), J302.a6
/Bus Tester Connector/USB-: J301.A7 (D-), J301.B7 (D-), J302.b6
GND: C301.2, J301.A1 (GND), J301.A12 (GND), J301.B1 (GND), J301.B12 (GND), J301.S1 (SHIELD), J302.a3, J302.a10, J302.b3, J302.b10, R301.2, R302.2, R303.2; also elsewhere on the board
unnamed: D301.1 (K), R303.1
unnamed: J302.a4, J302.a5, J302.b4, J302.b5, J303.1

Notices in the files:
pcb/bus/bus.kicad_pcb:
Copyright by
{dblquote}Amateurfunkclub für Remote Stationen{dblquote}
